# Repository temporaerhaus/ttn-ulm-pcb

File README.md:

# Münsterplatine – a pcb for LoRaWan

(Münsterplatine ist german for minster pcb.)

Welcome to the TTN Ulm Münsterplatine repository.
Our local TTN-community was under the impression that there is a tremendous need for a cheap and easy to use LoRaWan All-in-one kit, and so we created one.
The work is build around the ready-made arduino Pro Mini which can be bought from various sources for under 3 EUR per piece and the RFM96W LoRa tranceiver for communication.

After the board has been designed by the members of the community, we were sponsored by Initiative Ulm Digital that funded our initial production. 
Minsternode has then been prominently featured in many events, including the yearly conference of Initiave Ulm Digital and the event "Ulm Macht Zukunft".

# 2nd major version

(The most recent revision of this variant is v1.1)

In this version we added a multitude of goodies for you comfort as a LoRaWan-enthusiast. 
The features include:
* onboard FTDI and USB, so you can flash your Arduino easily by connecting it to your PC directly
* battery connector
* _battery charger_ included, so you can charge your LiPo-battery while plugged into the PC
* a combinded wire/ufl/sma connector is also onboard.
	
# 1st major version

This version aimed to satisfy you basic LoRaWan needs in form of a pcb on which the Arduino Pro Mini and the RMF95W-module can be soldered together. 
But beware: You still need a FTDI USB<->Serial converter to flash your Arduino. 
Since there is no additional hardware, this version is less energy-hungry than Version 2

You can find this version in the [legacy branch](https://github.com/verschwoerhaus/ttn-ulm-pcb/tree/legacy).

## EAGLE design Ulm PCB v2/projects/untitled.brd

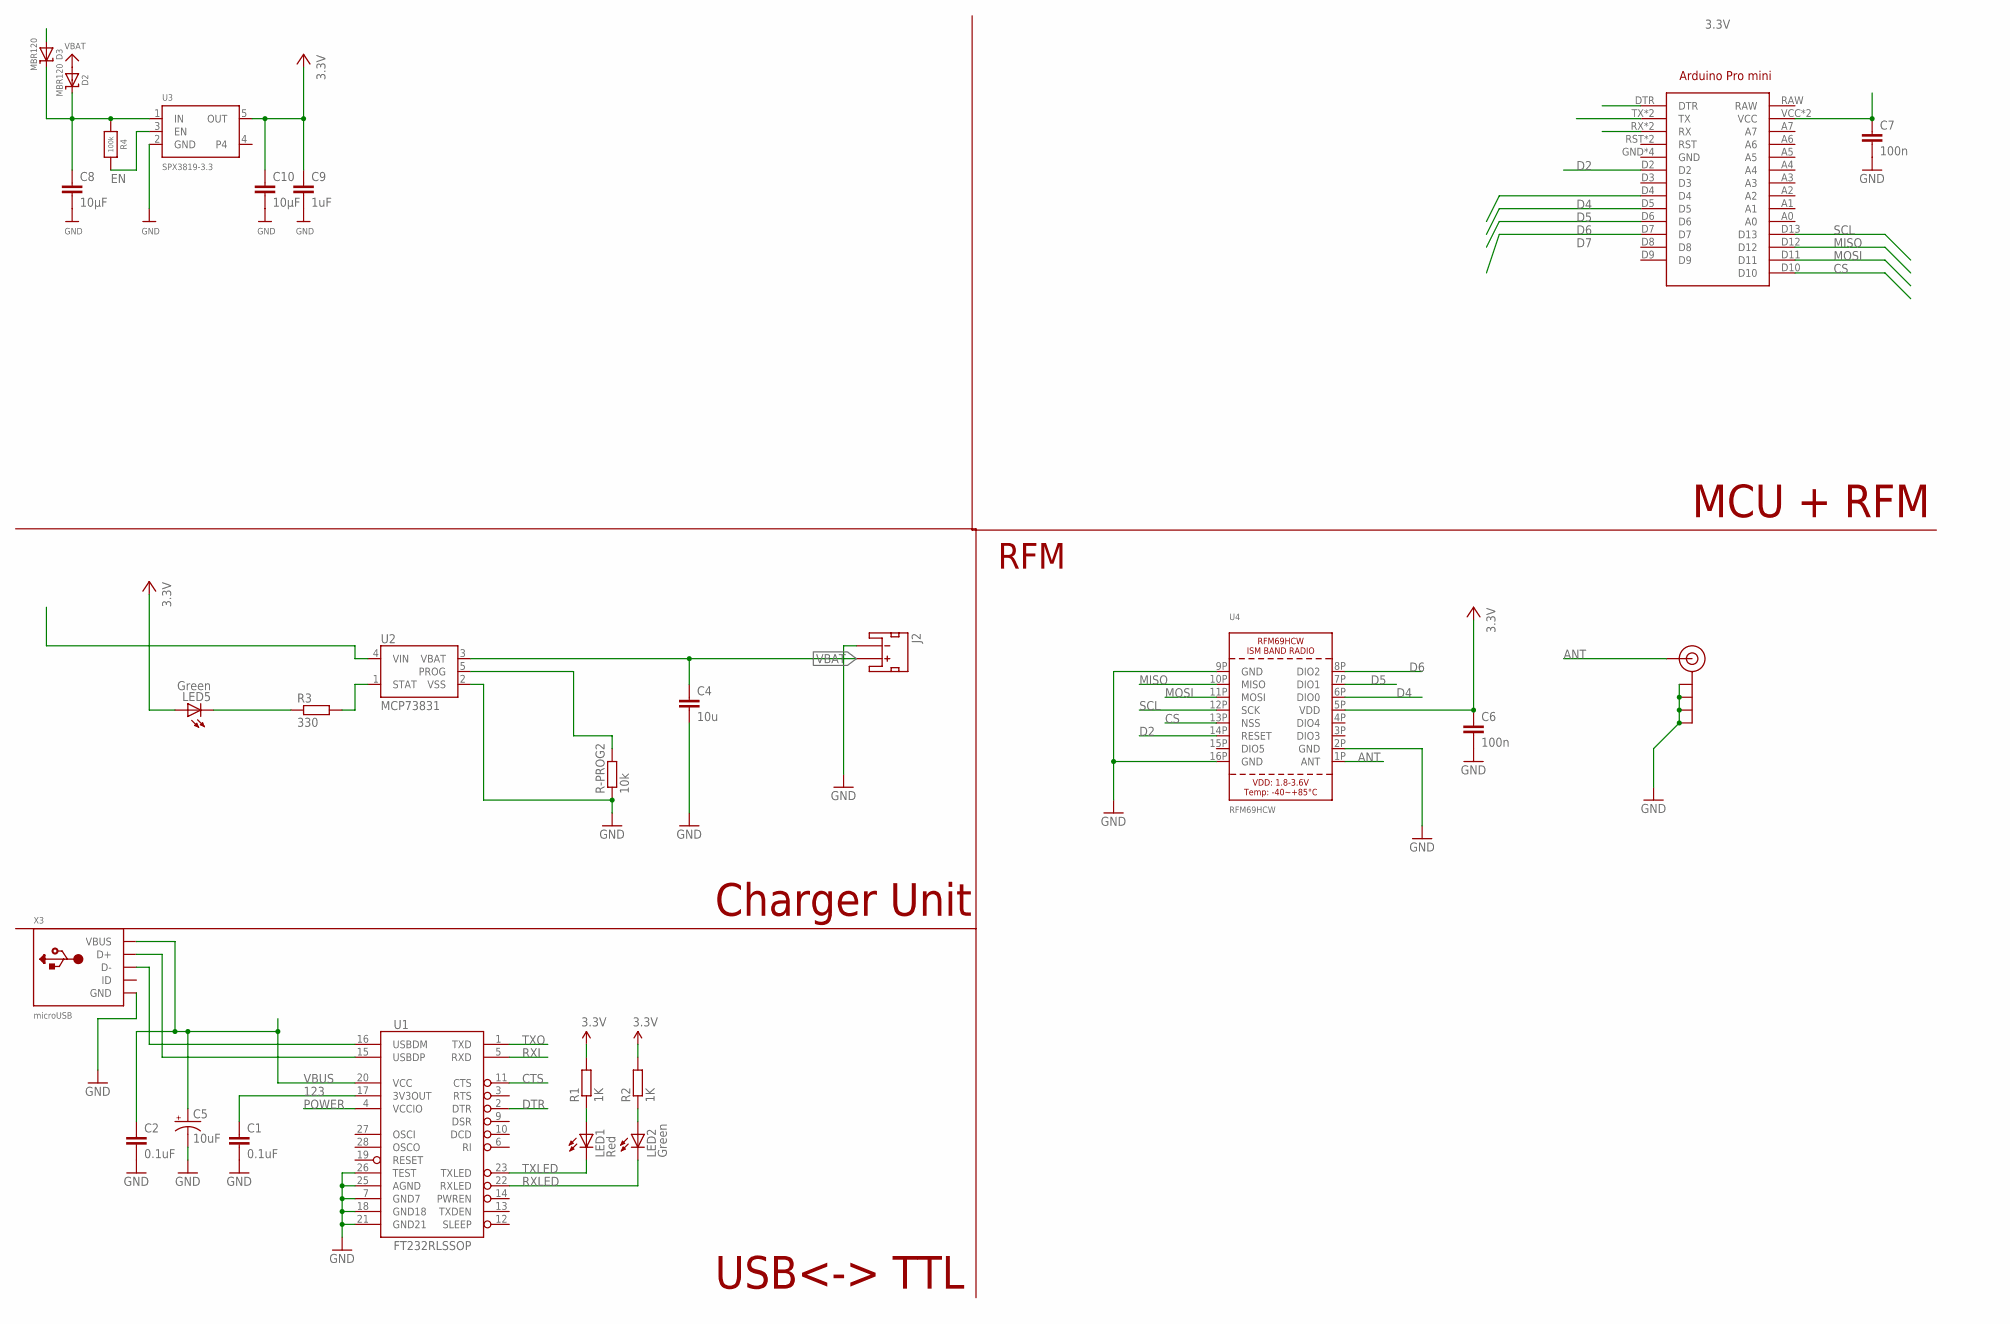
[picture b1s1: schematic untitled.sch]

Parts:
C1, C2: 0.1uF; C0805
C4: 10u; C0805
C5: 10uF; EIA3216
C6, C7: 100n; C0805
C8, C10: 10µF; C0805
C9: 1uF; C0805
D2, D3: MBR120; SOD-123
J2: JST_2MM_MALE; JST-2-SMD
J$2: ANTENNATINY; SMA_UFL_PAD_TINY
LED1: Red; LED-0603
LED2, LED5: Green; LED-0603
R1, R2: 1K; R0805
R3: 330; R0805
R4: 100k; 0603-NO
R-PROG2: 10k; R0805
U1: FT232RLSSOP; SSOP28DB
U2: MCP73831; SOT23-5
U3: SPX3819-3.3; SOT23-5
U4: RFM69HCW; RFMHCW_SMT
U$1: ARDUINO_PRO_MINI
X3: microUSB; 4UCONN_20329_V2

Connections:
3.3V: C6.1, C7.1, C9.1, C10.1, LED5.A, R1.2, R2.2, U3.5 (OUT), U4.5P (VDD), U$1.VCC, U$1.VCC@1 (VCC)
123: C1.1, U1.17 (3V3OUT)
ANT: J$2.ANT1 (SIGNAL), J$2.ANT2 (SIGNAL), J$2.ANT3 (SIGNAL), U4.1P (ANT)
CS: U4.13P (NSS), U$1.D10
CTS: U1.11 (CTS)
D2: U4.14P (RESET), U$1.D2
D4: U4.6P (DIO0), U$1.D4
D5: U4.7P (DIO1), U$1.D5
D6: U4.8P (DIO2), U$1.D6
D7: U$1.D7
DTR: U1.2 (DTR), U$1.DTR
EN: R4.2, U3.3 (EN)
GND: C1.2, C2.2, C4.2, C5.C (-), C6.2, C7.2, C8.2, C9.2, C10.2, J2.1 (-), J$2.GND1 (GND), J$2.GND2 (GND), J$2.GND3 (GND), J$2.GND4 (GND), R-PROG2.1, U1.7 (GND7), U1.18 (GND18), U1.21 (GND21), U1.25 (AGND), U1.26 (TEST), U2.2 (VSS), U3.2 (GND), U4.2P (GND), U4.9P (GND), U4.16P (GND), U$1.GND, U$1.GND@1 (GND), U$1.GND@2 (GND), U$1.GND@3 (GND), X3.BASE@1 (GND), X3.BASE@2 (GND), X3.GND, X3.SPRT@1 (GND), X3.SPRT@2 (GND), X3.SPRT@3 (GND), X3.SPRT@4 (GND); also elsewhere on the board
LOL: R-PROG2.2, U2.5 (PROG)
MEAS_VBAT: U$1.A0; also elsewhere on the board
MISO: U4.10P (MISO), U$1.D12
MOSI: U4.11P (MOSI), U$1.D11
unnamed: LED1.A, R1.1
unnamed: LED2.A, R2.1
unnamed: LED5.C, R3.1
unnamed: R3.2, U2.1 (STAT)
POWER: U1.4 (VCCIO)
RXI: U1.5 (RXD), U$1.TX, U$1.TX@1 (TX)
RXLED: LED2.C, U1.22 (RXLED)
SCL: U4.12P (SCK), U$1.D13
TXLED: LED1.C, U1.23 (TXLED)
TXO: U1.1 (TXD), U$1.RX, U$1.RX@1 (RX)
USB_D+: U1.15 (USBDP), X3.D+
USB_D-: U1.16 (USBDM), X3.D-
V5: C8.1, D2.C, D3.C, R4.1, U2.4 (VIN), U3.1 (IN)
VBAT: C4.1, D2.A, J2.2 (+), U2.3 (VBAT); also elsewhere on the board
VBUS: C2.1, C5.A (+), D3.A, U1.20 (VCC), X3.VBUS

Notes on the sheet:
USB<-> TTL
Charger Unit
MCU + RFM
RFM

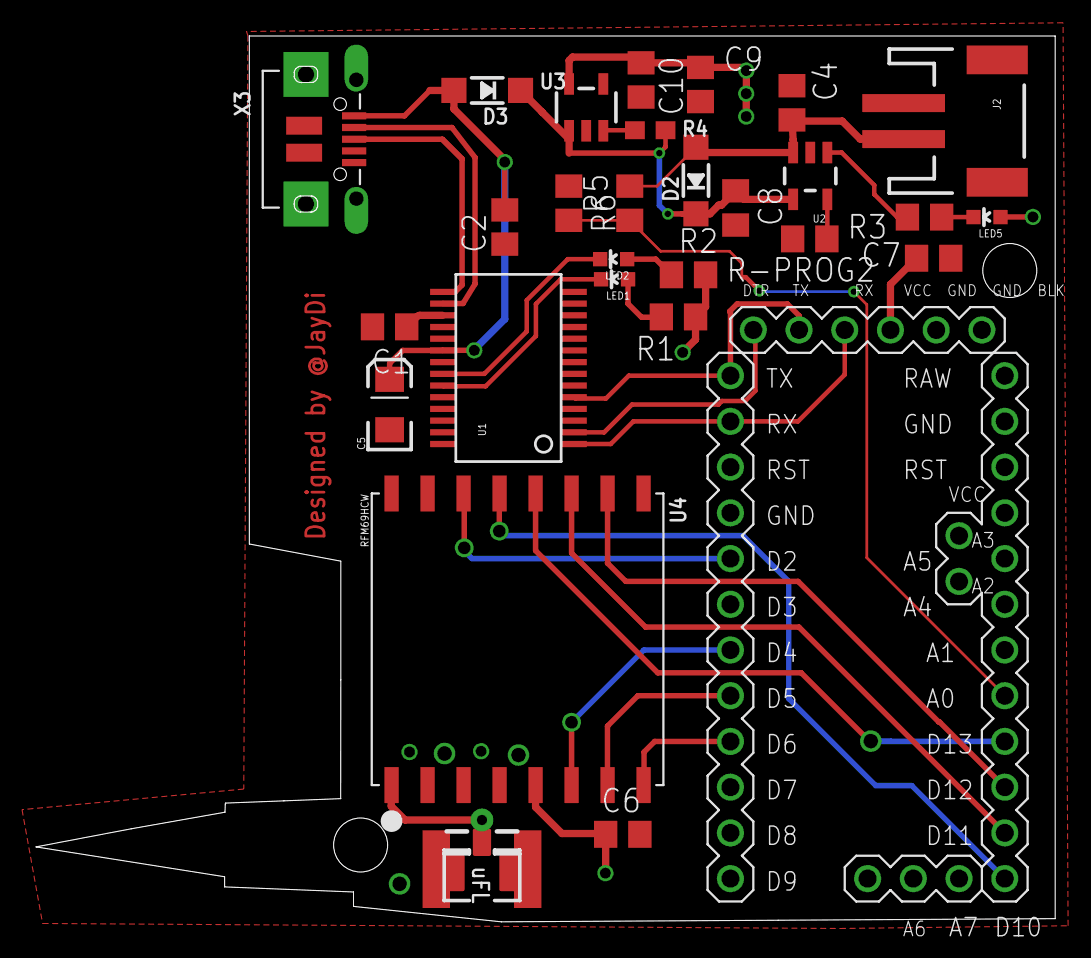
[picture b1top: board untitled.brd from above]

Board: 2 copper layers, 56.6 x 49.2 mm, 29 parts (0 on the bottom side), 29 nets.

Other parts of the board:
R5, R6: 100k; R0805

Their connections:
GND: R6.1; also elsewhere on the board
MEAS_VBAT: R5.1, R6.2; also elsewhere on the board
VBAT: R5.2; also elsewhere on the board

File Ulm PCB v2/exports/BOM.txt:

"Part";"Value";"Device";"Package";"Description";"PROD_ID";
"C1";"0.1uF";"C-EUC0805";"C0805";"CAPACITOR, European symbol";"";
"C2";"0.1uF";"C-EUC0805";"C0805";"CAPACITOR, European symbol";"";
"C4";"10u";"C-EUC0805";"C0805";"CAPACITOR, European symbol";"";
"C5";"10uF";"CAP_POL1206";"EIA3216";"Capacitor Polarized";"";
"C6";"100n";"C-EUC0805";"C0805";"CAPACITOR, European symbol";"";
"C7";"100n";"C-EUC0805";"C0805";"CAPACITOR, European symbol";"";
"C8";"10µF";"C-EUC0805";"C0805";"CAPACITOR, European symbol";"";
"C9";"1uF";"C-EUC0805";"C0805";"CAPACITOR, European symbol";"";
"C10";"10µF";"C-EUC0805";"C0805";"CAPACITOR, European symbol";"";
"D2";"MBR120";"DIODE-SCHOTTKYSOD-123";"SOD-123";"";"";
"J$2";"ANTENNATINY";"ANTENNATINY";"SMA_UFL_PAD_TINY";"SMA Antenna Connector";"";
"J2";"";"JST_2MM_MALE";"JST-2-SMD";"Mates to single-cell LiPo batteries.";"CONN-08352";
"LED1";"Red";"LED0603";"LED-0603";"LEDs";"";
"LED2";"Green";"LED0603";"LED-0603";"LEDs";"";
"LED5";"Green";"LED0603";"LED-0603";"LEDs";"";
"R-PROG2";"10k";"R-EU_R0805";"R0805";"RESISTOR, European symbol";"";
"R1";"1K";"R-EU_R0805";"R0805";"RESISTOR, European symbol";"";
"R2";"1K";"R-EU_R0805";"R0805";"RESISTOR, European symbol";"";
"R3";"330";"R-EU_R0805";"R0805";"RESISTOR, European symbol";"";
"R4";"100k";"RESISTOR_0603_NOOUT";"0603-NO";"Resistors";"";
"U$1";"";"ARDUINO_PRO_MINI";"ARDUINO_PRO_MINI";"For creating Arduino Pro Mini shields";"";
"U1";"FT232RLSSOP";"FT232RLSSOP";"SSOP28DB";"USB UART";"";
"U2";"MCP73831";"MCP73831";"SOT23-5";"Miniature single cell, fully integrated Li-Ion, Li-polymer charge management controller";"IC-09995";
"U3";"SPX3819-3.3";"VREG_SOT23-5";"SOT23-5";"SOT23-5 Fixed Voltage Regulators";"";
"U4";"RFM69HCW";"RFM69HCW_SMT";"RFMHCW_SMT";"RFM69HCW - ISM Band RF Transceiver";"";
"X3";"microUSB";"USB_MICRO_20329_V2";"4UCONN_20329_V2";"USB Connectors";"";

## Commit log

2017-07-06 initital commit
2017-07-11 Version 2 hinzugefügt. Todo: * Add Voltage Regulator (wire up) * Add other ProMini-Designs * Credits
2017-07-11 connected \!DTR Pin to RST
2017-07-13 reworked layout. Added voltage controller and discharging mechanism
2017-07-13 prinzipiell Produktionsreif. Todo: Verkürzen
2017-07-13 Technische Arbeiten abgeschlossen. Logo fehlt noch
2017-07-13 refactored file structure, updated README
2017-07-13 rerouted rmf power suppyl
2017-07-13 rerouted arduino power suppyl
2017-07-13 nicing of batterycharger
2017-07-15 Create LICENSE
2017-07-15 add calculations fpr v2
2017-07-15 banished macs .DS_STORE files... grml
2017-07-16 WIP: reducing height. Antenna must be refitted
2017-07-16 Board now approx 5x4 cm
2017-07-16 Successful designrule check
2017-07-16 corrected gnd path to FT232RL
2017-07-16 corrected one polygon. made antenna trace shorter
2017-07-20 replaced some parts with their bigger equivalent
2017-07-20 updated calc sheets with arduino pro mini 328p. Kudos to Simon Fuchs
2017-07-31 richtiges Arduino Pro Mini Pinout hinzugefügt
2017-07-31 nicing of some traces
2017-08-03 Added images with Ulmer Münster Solhouette.
2017-08-03 rerouted traces to make room for the big M ( =muenster)
2017-08-03 reduced colors to 2 in UlmerMünsterSilhouette.bmp
2017-08-03 #+-%&$§%&T$ picture editing.
2017-08-03 added picture of board layout
2017-08-03 Revert "added picture of board layout"
    This reverts commit 6c2dd7b23edb37982c4fb7cb2418e2451a8ef545.
2017-08-03 added new board layout
2017-08-20 Deployed Münsterdesign
2017-08-21 replaced some of the 0603 Resistors with 0805
2017-08-22 Added remaining Logos on backside silkscreen
2017-08-22 corrected one DRC-Error
2017-08-23 moved logos slightly. Tried correcting muenster's imbalance
2017-08-23 Finalized design
2017-08-23 Cam-processed
2017-08-23 added order information
2017-08-23 updated order list
2017-08-23 Last time: updated Orderlist
2017-08-23 added panelized gerber files
2017-08-23 panelized
2017-08-24 Create AUTHORS
2017-09-08 added v3 of backplate logos
2017-09-13 Fixed Bug regarding Pinout of RFM95W
2017-09-13 Added new back panel logos
2017-09-13 corrected DRC-Errors. ToDo: Right USB Slot, Diode vs. Jumper
2017-09-13 Final Final
2017-09-13 Gerber Files v2
2017-09-14 added new panelized gerber files
2017-09-14 Fixed Cap. Values for better voltage stabilazation
2017-09-22 added microUSB
2017-09-24 Added Cam-Job. Gerber Gerber Gerber
2018-01-31 Updated Design. Fixed last bugs. Updated BOM
2018-01-31 Updated BOM
2018-02-19 Added clean
2018-06-13 added battery voltage monitoring
2018-08-31 Generated Gerber-files for enhanced pcb-layout
2018-10-28 Refactored directory structure. Added some screenshots for the sake of docu
2018-10-28 Added example code; added first draft of QA code.
2021-04-15 Added some details to the history of the project

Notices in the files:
parts and their libraries:
SparkFun-PowerIC: Licensing: CC v3.0 Share-Alike You are welcome to use this library for commercial purposes.
microbuilder: This work is placed in the public domain, and may be freely used for commercial and non-commercial work with the following conditions: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
